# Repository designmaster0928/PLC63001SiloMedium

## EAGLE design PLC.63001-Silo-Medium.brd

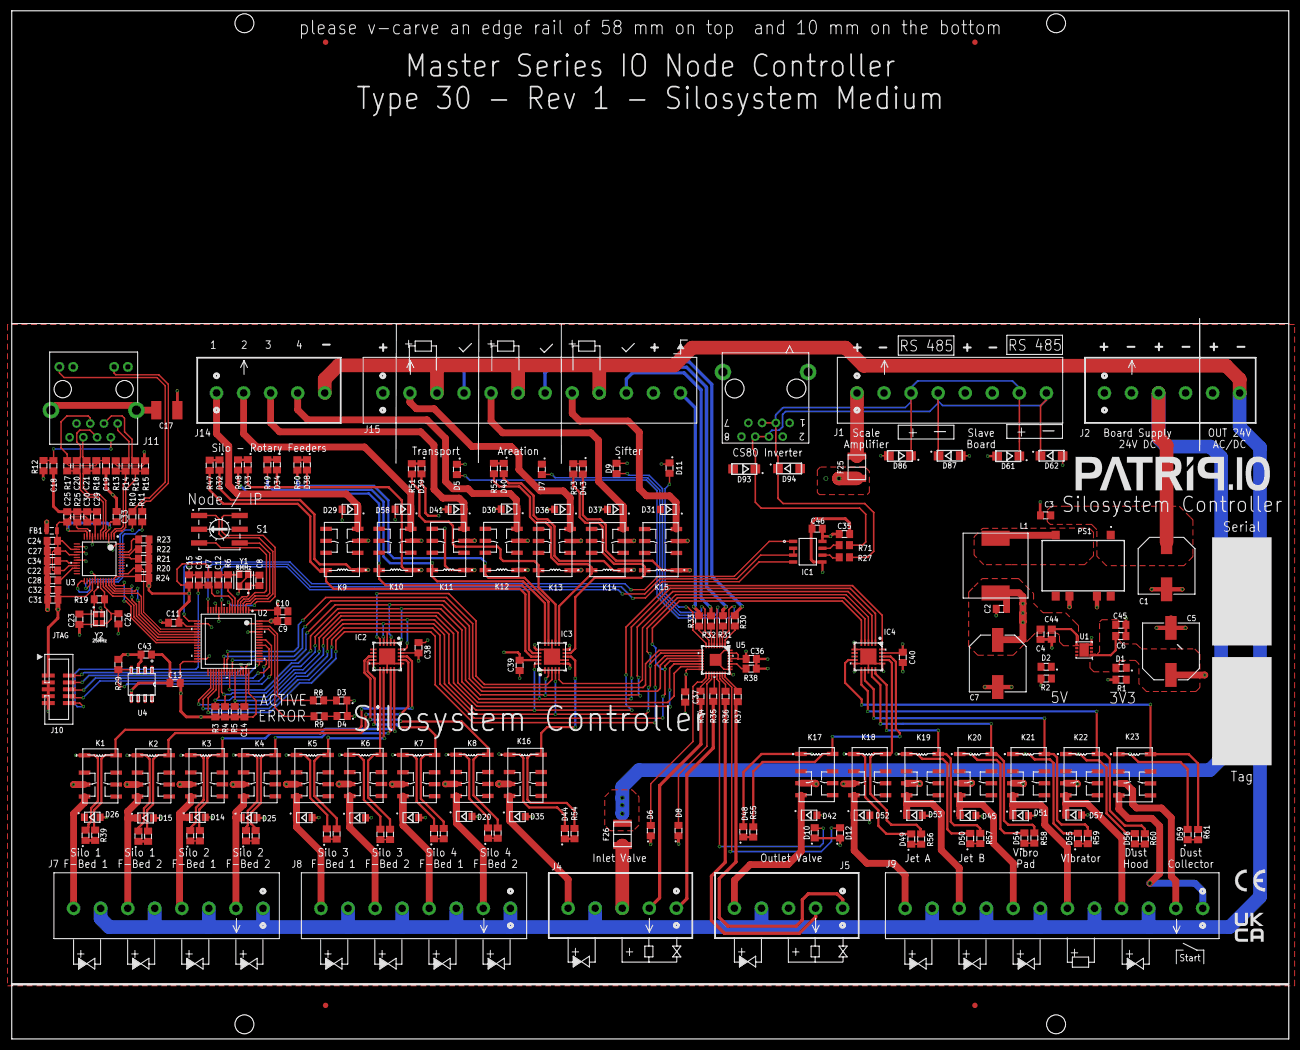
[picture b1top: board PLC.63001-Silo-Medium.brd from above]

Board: 4 copper layers, 236.0 x 190.0 mm, 261 parts (0 on the bottom side), 172 nets.

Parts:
C1, C5, C7: C-220U-10X10; CAPAE1030X1050N
C2, C6, C16, C22, C24, C25, C27, C29, C30, C31, C37: C-1U-0805; C0805
C3, C4, C9, C10, C11, C13, C14, C35, C36, C38, C39, C40, C43, C44, C45: C-100N-0805; C0805
C8, C12, C23, C26: C-18P-0805; C0805
C15, C32, C33: C-10U-0805; C0805
C17: C-1N-1812; C1812
C18: C-22N-0805; C0805
C19, C28: C-10N-0805; C0805
C20, C21: C-68N-0805; C0805
C34, C46: C-4U7-0805; C0805
D1, D2, D6, D8, D10, D11, D12, D16, D17, D18, D22, D23, D24, D27, D28, D32, D33, D34, D38, D39, D40, D43, D44, D48, D49, D50, D54, D55, D56, D59: LED-GREEN-0805; L0805
D3: LED-BLUE-0805; L0805
D4, D5, D7, D9: LED-RED-0805; L0805
D13, D14, D15, D19, D20, D21, D25, D26, D29, D30, D31, D35, D36, D37, D41, D42, D45, D51, D52, D53, D57, D58: SMAJ30CA; SOD123FL
D61, D62, D86, D87, D93, D94: SMAJ30CA; DO214AC
F25, F26: F-1500MA; FUSC4632X75N
FB1: FB-120R; HANDHELDMAINBOARD2_0805L
IC1: MAX-3486; SOIC127P600X175-8N
IC2, IC3, IC4: MAX-4896; QFN65P500X500X80-21N
J1: OMN_5_08; CONN_08_OMN
J2: OMN_5_06; CONN6_8000072438_WED
J4, J5: OMN_5_05; CONN_05_OMN_ROT
J7, J8: OMN_5_08; CONN_08_OMN_ROT
J9: OMN_5_12; CONN12_8000072470_WED_ROT
J10: IDC-10-HP; 2X05_1.27MM_BOX_NOPOSTS
J11: NET-MAG-LED_THR_180; CONN14_2562150000_WED
J13: NET-THR_180; CONN8_2562970000_WED
J14: OMN_5_05; CONN_05_OMN
J15: OMN_5_12; CONN12_8000072470_WED
K1, K2, K3, K4, K5, K6, K7, K8, K9, K10, K11, K12, K13, K14, K15, K16, K17, K18, K19, K20, K21, K22, K23: HFD4-5; HFD45S
L1: ID-100UH; INDPM120120X100N
PS1: TSR1-2450SM; TSR124120SM
R1, R2, R39, R40, R41, R42, R43, R44, R45, R46, R47, R48, R49, R50, R51, R52, R53, R54, R55, R56, R57, R58, R59, R60, R61: R-220-0805; R0805
R3, R4, R29: R-4K7-0805; R0805
R5, R7, R20, R21, R22, R23, R24: R-10K-0805; R0805
R6: R-390-0805; R0805
R8, R9: R-120-0805; R0805
R10, R11: R-2K2-0805; R0805
R12: R-10-0805; R0805
R13, R15, R17, R18: R-49R9-0805; R0805
R14, R16: R-33-0805; R0805
R19: R-1M-0805; R0805
R25: R-12K4-0805; R0805
R27, R71: PTC; R0805
R30, R31, R32, R33, R35, R36, R37: R-1K5-0805; R0805
R34: R-1K-0805; R0805
R38: R-5K2-0805; R0805
S1: SWT-10P; 42854232081X_10POS
U1: LDO-5V-3V3; NCV8165ML330TBG
U2: STM32F103RB; ST_MICROELECTRONICS_STM32F103RBT6_0
U3: W5500; WIZNET_W5500_0
U4: DS18B20Z; 21-0041B_8_MXM
U5: MAX-22199; 21-0140_T3255+6_MXM
U$1, U$34: RS485
U$2: LOGO-UKCA
U$3: CE-4MM
U$4, U$5, U$6, U$7, U$8, U$26, U$27, U$28, U$29, U$30, U$32, U$33: SS_SOLENOID
U$9, U$12, U$14, U$22, U$23, U$35, U$38: SS_P
U$10, U$11, U$13, U$24, U$25, U$36: SS_M
U$15, U$18, U$39: SS_CONTACTOR_180
U$16, U$17: SS_SOLSEN
U$19: SS_CONTACTOR
U$20: LOGO-PATRIQ
U$31: BASEBOARD_TOOLING; _THL_VP
U$37, U$40, U$41: SS_CHECK
U$42: SS_SIG
U$43: SS_SERIAL_TAG
Y1: QRZ-8MHZ; 4-SMD3.2X2.5MM,NOLEAD
Y2: QRZ-25MHZ; ECS2501836B2CTYTR

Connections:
1V2O: C28.1, U3.22
24V_1: F25.1, J15.1, J15.11
24V_2: F26.1, J4.3, J5.3
+3V3: C5.1, C6.1, C9.1, C10.1, C11.1, C13.1, C14.1, C15.1, C31.1, C32.1, C35.1, C36.1, C37.1, C38.1, C39.1, C40.1, C43.2, C45.1, C46.1, D1.A, FB1.2, IC1.8, IC2.19, IC3.19, IC4.19, J10.1, J11.12, J11.14, R3.2, R4.2, R5.2, R7.2, R12.2, R13.2, R15.2, R20.2, R21.2, R22.2, R23.2, R24.2, R29.2, U1.1, U2.1, U2.13, U2.19, U2.32, U2.48, U2.64, U3.28, U4.3, U5.16, U5.28, U5.29, U5.31
+5V: C2.1, C4.1, C7.1, C44.1, D2.A, D16.A, D17.A, D18.A, D22.A, D23.A, D24.A, D27.A, D28.A, D32.A, D33.A, D34.A, D38.A, D39.A, D40.A, D43.A, D44.A, D48.A, D49.A, D50.A, D54.A, D55.A, D56.A, D59.A, K1.1, K2.1, K3.1, K4.1, K5.1, K6.1, K7.1, K8.1, K9.1, K10.1, K11.1, K12.1, K13.1, K14.1, K15.1, K16.1, K17.1, K18.1, K19.1, K20.1, K21.1, K22.1, K23.1, L1.2, U1.5, U1.8
+24V: C1.1, C3.1, F25.2, F26.2, J1.1, J1.5, J2.1, J2.3, PS1.1
ACTLED: R10.2, U3.27
AVDD: C22.1, C24.1, C25.1, C27.1, C29.1, C30.1, C33.1, FB1.1, U3.4, U3.8, U3.11, U3.15, U3.17, U3.21
EXRES1: R25.2, U3.10
GND: C1.2, C2.2, C3.2, C4.2, C5.2, C6.2, C7.2, C8.2, C9.2, C10.2, C11.2, C12.2, C13.2, C14.2, C15.2, C16.2, C17.1, C18.1, C19.2, C22.2, C23.2, C24.2, C25.2, C26.2, C27.2, C28.2, C29.2, C30.2, C31.2, C32.2, C33.2, C34.2, C35.2, C36.2, C37.2, C38.2, C39.2, C40.2, C43.1, C44.2, C45.2, C46.2, D3.C, D4.C, D5.C, D6.C, D7.C, D8.C, D9.C, D10.C, D11.C, D12.C, D13.A, D14.A, D15.A, D19.A, D20.A, D21.A, D25.A, D26.A, D29.A, D30.A, D31.A, D35.A, D36.A, D37.A, D41.A, D42.A, D45.A, D51.A, D52.A, D53.A, D57.A, D58.A, D61.A, D62.A, D86.A, D87.A, D93.A, D94.A, IC1.5, IC2.6, IC2.7, IC2.10, IC2.13, IC2.16, IC2.21, IC3.6, IC3.7, IC3.10, IC3.13, IC3.16, IC3.21, IC4.6, IC4.7, IC4.10, IC4.13, IC4.16, IC4.21, J1.2, J1.6, J2.2, J2.4, J10.3, J10.5, J10.7, J10.9, J11.8, J13.1, PS1.7, PS1.9, R1.1, R2.1, R25.1, R38.1, S1.C1, S1.C2, U1.4, U1.9, U2.12, U2.18, U2.31, U2.47, U2.60, U2.63, U3.3, U3.9, U3.14, U3.16, U3.19, U3.29, U3.48, U4.5, U5.25, U5.26, U5.32, U5.33, Y1.2, Y1.4, Y2.2, Y2.4
GNDI: C17.2, J11.15, J11.16
INPUT1: J15.4, R30.1
INPUT1_LED: D5.A, U5.2
INPUT2: J15.7, R31.1
INPUT2_LED: D7.A, U5.4
INPUT3: J15.10, R32.1
INPUT3_LED: D9.A, U5.6
INPUT4: J15.12, R33.1
INPUT4_LED: D11.A, U5.8
INPUT5: J4.4, R34.1
INPUT5_LED: D6.A, U5.17
INPUT6: J4.5, R35.1
INPUT6_LED: D8.A, U5.19
INPUT7: J5.4, R36.1
INPUT7_LED: D10.A, U5.21
INPUT8: J5.5, R37.1
INPUT8_LED: D12.A, U5.23
IN_!FAULT!: R3.1, U2.37, U5.14
IN_!LATCH!: U2.39, U5.12
IN_!READY!: R4.1, U2.38, U5.15
JTCK/SWCLK: J10.4, U2.49
JTDI: J10.8, U2.50
JTDO: J10.6, U2.55
JTMS/SWDIO: J10.2, U2.46
LED_ACT: R8.1, U2.62
LED_ERROR: R9.1, U2.61
LINKLED: R11.2, U3.25
unnamed: R38.2, U5.27
unnamed: IC1.7, R71.1
unnamed: D48.C, R55.1
unnamed: D54.C, R58.1
unnamed: D17.C, R40.1
unnamed: D59.C, R61.1
unnamed: D55.C, R59.1
unnamed: D2.C, R2.2
unnamed: D22.C, R42.1
unnamed: D27.C, R45.1
unnamed: D50.C, R57.1
unnamed: D23.C, R43.1
unnamed: D28.C, R46.1
unnamed: D18.C, R41.1
unnamed: D24.C, R44.1
unnamed: D56.C, R60.1
unnamed: IC1.6, R27.1
unnamed: D49.C, R56.1
unnamed: R30.2, U5.1
unnamed: R31.2, U5.3
unnamed: R32.2, U5.5
unnamed: R33.2, U5.7
unnamed: R34.2, U5.18
unnamed: R35.2, U5.20
unnamed: R36.2, U5.22
unnamed: R37.2, U5.24
unnamed: D32.C, R47.1
unnamed: D38.C, R50.1
unnamed: D43.C, R53.1
unnamed: C12.1, R6.1, Y1.3
unnamed: D39.C, R51.1
unnamed: D44.C, R54.1
unnamed: D34.C, R49.1
unnamed: D40.C, R52.1
unnamed: D33.C, R48.1
unnamed: D16.C, R39.1
unnamed: D1.C, R1.2
unnamed: C19.1, J11.5, R17.1, R18.1
unnamed: J11.11, R10.1
unnamed: J11.13, R11.1
unnamed: L1.1, PS1.5
unnamed: D3.A, R8.2
unnamed: D4.A, R9.2
NET_G4: C18.2, J11.2, R12.1
NET_ID0: S1.1, U2.2
NET_ID1: S1.2, U2.3
NET_ID2: S1.4, U2.4
NET_ID3: S1.8, U2.8
NET_R+: C20.2, J11.4
NET_R-: C21.2, J11.6
NET_T+: J11.1, R14.1
NET_T-: J11.3, R16.1
NRST: C16.1, J10.10, R7.1, U2.7
OSCIN: C8.1, U2.5, Y1.1
OSCOUT: R6.2, U2.6
OSR1_OUT: IC2.5, IC3.3
OSR1_OUT1: IC2.18, K1.8, R39.2
OSR1_OUT2: IC2.17, K2.8, R40.2
OSR1_OUT3: IC2.15, K3.8, R41.2
OSR1_OUT4: IC2.14, K4.8, R42.2
OSR1_OUT5: IC2.12, K5.8, R43.2
OSR1_OUT6: IC2.11, K6.8, R44.2
OSR1_OUT7: IC2.9, K7.8, R45.2
OSR1_OUT8: IC2.8, K8.8, R46.2
OSR2_OUT: IC3.5, IC4.3
OSR2_OUT1: IC3.18, K9.8, R47.2
OSR2_OUT2: IC3.17, K10.8, R48.2
OSR2_OUT3: IC3.15, K11.8, R49.2
OSR2_OUT4: IC3.14, K12.8, R50.2
OSR2_OUT5: IC3.12, K13.8, R51.2
OSR2_OUT6: IC3.11, K14.8, R52.2
OSR2_OUT7: IC3.9, K15.8, R53.2
OSR2_OUT8: IC3.8, K16.8, R54.2
OSR3_OUT1: IC4.18, K17.8, R55.2
OSR3_OUT2: IC4.17, K18.8, R56.2
OSR3_OUT3: IC4.15, K19.8, R57.2
OSR3_OUT4: IC4.14, K20.8, R58.2
OSR3_OUT5: IC4.12, K21.8, R59.2
OSR3_OUT6: IC4.11, K22.8, R60.2
OSR3_OUT7: IC4.9, K23.8, R61.2
OUT1: D26.C, J7.1, K1.4
OUT2: D15.C, J7.3, K2.4
OUT3: D14.C, J7.5, K3.4
OUT4: D25.C, J7.7, K4.4
OUT5: D19.C, J8.1, K5.4
OUT6: D13.C, J8.3, K6.4
OUT7: D21.C, J8.5, K7.4
OUT8: D20.C, J8.7, K8.4
OUT9: D29.C, J14.1, K9.4
OUT10: D58.C, J14.2, K10.4
OUT11: D41.C, J14.3, K11.4
OUT12: D30.C, J14.4, K12.4
OUT13: D36.C, J15.2, K13.4
OUT14: D37.C, J15.5, K14.4
OUT15: D31.C, J15.8, K15.4
OUT16: D35.C, J4.1, K16.4
OUT17: D42.C, J5.1, K17.4
OUT18: D52.C, J9.1, K18.4
OUT19: D53.C, J9.3, K19.4
OUT20: D45.C, J9.5, K20.4
OUT21: D51.C, J9.7, K21.4
OUT22: D57.C, J9.9, K22.4
OUT23-3: J9.11, K23.3
OUT23-4: J9.12, K23.4
OUT+: J2.5, K1.3, K2.3, K3.3, K4.3, K5.3, K6.3, K7.3, K8.3, K9.3, K10.3, K11.3, K12.3, K13.3, K14.3, K15.3, K16.3, K17.3, K18.3, K19.3, K20.3, K21.3, K22.3
OUT-: J2.6, J4.2, J5.2, J7.2, J7.4, J7.6, J7.8, J8.2, J8.4, J8.6, J8.8, J9.2, J9.4, J9.6, J9.8, J9.10, J14.5, J15.3, J15.6, J15.9
OUT_!FLAG!: IC2.20, IC3.20, IC4.20, R5.1, U2.43
OUT_!RESET!: IC2.1, IC3.1, IC4.1, U2.41
PMODE0: R23.1, U3.45
PMODE1: R22.1, U3.44
PMODE2: R21.1, U3.43
RS485_A+: D61.C, D86.C, D94.C, J1.3, J1.7, J13.3, J13.5, R27.2
RS485_B-: D62.C, D87.C, D93.C, J1.4, J1.8, J13.4, J13.6, R71.2
RS485_DIR: IC1.2, IC1.3, U2.11
RS485_RX: IC1.1, U2.17
RS485_TX: IC1.4, U2.16
RX_N: C21.1, R18.2, U3.5
RX_P: C20.1, R17.2, U3.6
SPI1_!CS!_NET: U2.24, U3.32
SPI1_MISO: U2.22, U3.34
SPI1_MOSI: U2.23, U3.35
SPI1_SCK: U2.21, U3.33
SPI2_!CS!_INP1: U2.40, U5.9
SPI2_!CS!_OUT: IC2.2, IC3.2, IC4.2, U2.42
SPI2_MISO: IC4.5, U2.35, U5.13
SPI2_MOSI: IC2.3, U2.36, U5.11
SPI2_SCK: IC2.4, IC3.4, IC4.4, U2.34, U5.10
SWB_TEMPS: R29.1, U2.57, U4.4
TOCAP: C34.1, U3.20
TX_N: R15.1, R16.2, U3.1
TX_P: R13.1, R14.2, U3.2
W5500_!INT!: R24.1, U2.25, U3.36
W5500_!RST!: R20.1, U2.20, U3.37
XI: C23.1, R19.2, U3.30, Y2.1
XO: C26.1, R19.1, U3.31, Y2.3

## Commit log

2023-08-01 first step
2023-08-03 third step
2023-08-07 step 5
2023-08-13 work-8.12

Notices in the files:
parts and their libraries:
COPYRIGHT: Copyright (C) 2022 Ultra Librarian. All rights reserved.
